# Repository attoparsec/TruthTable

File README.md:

# TruthTable
Eurorack Truth Table module

Full description: https://youtu.be/MvsgOZwyrD4

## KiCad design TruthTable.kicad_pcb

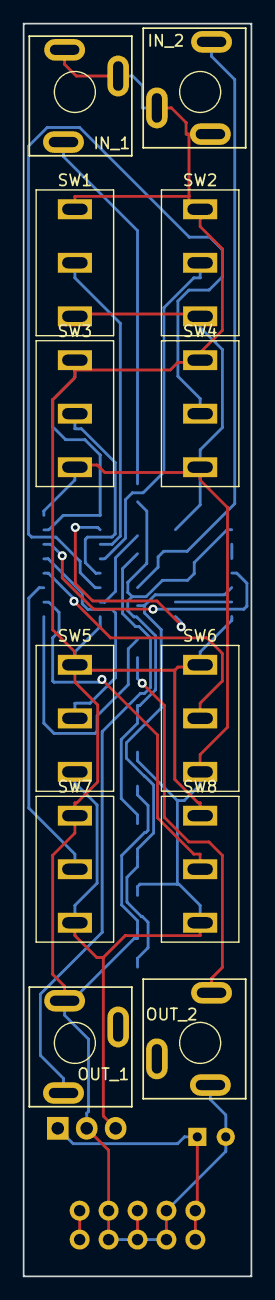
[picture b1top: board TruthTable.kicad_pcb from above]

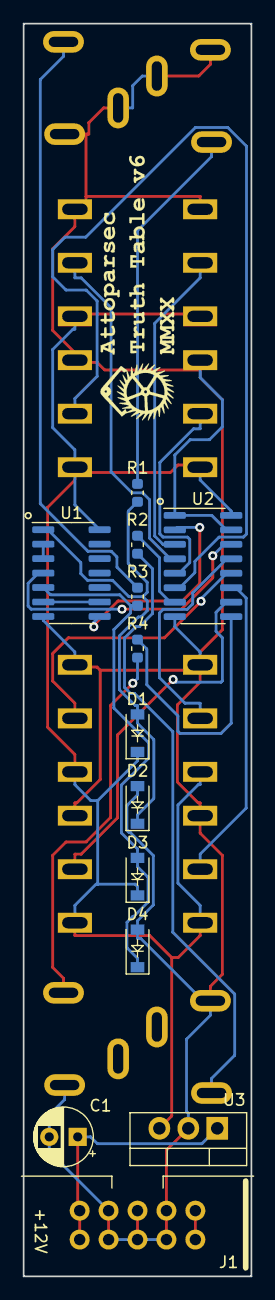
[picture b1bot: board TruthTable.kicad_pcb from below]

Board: 2 copper layers, 20.0 x 110.0 mm, 25 parts (13 on the bottom side), 24 nets.

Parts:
C1: 22U; CP_Radial_D5.0mm_P2.50mm
D1, D2, D3, D4: D; D_SOD-123
IN_1, IN_2: PJ301
J1: Conn_02x05_Odd_Even; Shrouded_power_header
OUT_1, OUT_2: PJ301
R1, R2, R3, R4: 1K; R_0603_1608Metric
SW1, SW2, SW3, SW4, SW5, SW6, SW7, SW8: SW_SPDT; 54-302PC_SPDT
U1: 74HC14; SOIC-14_3.9x8.7mm_P1.27mm
U2: 74LS153; SOIC-16_3.9x9.9mm_P1.27mm
U3: L7805; TO-220-3_Vertical

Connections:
+5V: D1.1, D3.1, SW1.1, SW2.1, SW3.1, SW4.1, SW5.1, SW6.1, SW7.1, SW8.1, U1.14, U2.16, U3.3
+12V: C1.1, J1.1, J1.2, U3.1
-12V: J1.9, J1.10
GND: C1.2, D2.2, D4.2, IN_1.1, IN_1.2, IN_2.1, IN_2.2, J1.3, J1.4, J1.5, J1.6, J1.7, J1.8, OUT_1.1, OUT_2.1, SW1.3, SW2.3, SW3.3, SW4.3, SW5.3, SW6.3, SW7.3, SW8.3, U1.7, U2.1, U2.8, U2.15, U3.2
IN_1: U1.4, U2.14
IN_2: U1.8, U2.2
unnamed: D1.2, D2.1, R1.1, U1.1
unnamed: D3.2, D4.1, R3.1, U1.5
unnamed: IN_1.3, R1.2
unnamed: IN_2.3, R3.2
unnamed: OUT_1.3, R2.1
unnamed: OUT_2.3, R4.1
unnamed: U1.2, U1.3
unnamed: U1.6, U1.9
OUT_1: R2.2, U2.7
OUT_2: R4.2, U2.9
TRUTH_1_A_B: SW1.2, U2.3
TRUTH_1_A_NB: SW3.2, U2.5
TRUTH_1_NA_B: SW2.2, U2.4
TRUTH_1_NA_NB: SW4.2, U2.6
TRUTH_2_A_B: SW5.2, U2.13
TRUTH_2_A_NB: SW7.2, U2.11
TRUTH_2_NA_B: SW6.2, U2.12
TRUTH_2_NA_NB: SW8.2, U2.10

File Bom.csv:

"Manufacturer Part Number","Manufacturer","Digi-Key Part Number","Customer Reference","Reference Designator","Packaging","Part Status","Quantity","Unit Price","Extended Price","Quantity Available","Mfg Std Lead Time","Description","RoHS Status","Lead Free Status","REACH Status"
"UVR1H220MDD1TD","Nichicon","493-6098-1-ND","","","Cut Tape (CT)","Active","1","0.27000","$0.27","5185","21 Weeks","CAP ALUM 22UF 20% 50V RADIAL","ROHS3 Compliant","Lead free","REACH Unaffected"
"302-S101","On Shore Technology Inc.","ED1543-ND","","","Bulk","Active","1","0.28000","$0.28","37383","9 Weeks","CONN HEADER VERT 10POS 2.54MM","ROHS3 Compliant","Lead free","REACH Unaffected"
"L7805CV","STMicroelectronics","497-1443-5-ND","","","Tube","Active","1","0.50000","$0.50","44639","10 Weeks","IC REG LINEAR 5V 1.5A TO220AB","ROHS3 Compliant","Lead free","REACH Unaffected"
"4832.2211","Schurter Inc.","486-3418-ND","","","Bulk","Active","4","1.50000","$6.00","1118","23 Weeks","CONN JACK MONO 3.5MM PNL MNT","ROHS3 Compliant","Lead free","REACH Unaffected"
"RC0603JR-071KL","Yageo","311-1.0KGRCT-ND","","","Cut Tape (CT)","Active","10","0.01700","$0.17","7042135","24 Weeks","RES SMD 1K OHM 5% 1/10W 0603","ROHS3 Compliant","Lead free","REACH Unaffected"
"SN74LS153DR","Texas Instruments","296-SN74LS153DRCT-ND","","","Cut Tape (CT)","Active","1","0.93000","$0.93","2410","6 Weeks","IC MULTIPLEXER 2 X 4:1 16SOIC","ROHS3 Compliant","Lead free","REACH Unaffected"
"SN74HC14DR","Texas Instruments","296-1194-1-ND","","","Cut Tape (CT)","Active","1","0.41000","$0.41","117017","12 Weeks","IC INVERTER SCHMITT 6CH 14SOIC","ROHS3 Compliant","Lead free","REACH Unaffected"
"BAT42W-TP","Micro Commercial Co","BAT42WTPMSCT-ND","","","Cut Tape (CT)","Active","5","0.37000","$1.85","76777","12 Weeks","DIODE SCHOTTKY 30V 200MA SOD123","ROHS3 Compliant","Lead free","REACH Unaffected"
"ANT11SEBQE","CIT Relay and Switch","2449-ANT11SEBQE-ND","","","Bulk","Active","8","1.64000","$13.12","292","8 Weeks","SWITCH TOGGLE SPDT SOLDER SEAL","RoHS Compliant","Not Available","Not Available"

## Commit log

2021-01-11 Initial checkin
2021-02-05 Updated labels
    Updated labels in the schematic to match the final naming scheme used on the panel
